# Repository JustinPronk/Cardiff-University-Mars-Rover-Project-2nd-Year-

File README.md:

# Rover Control PCB

Custom PCB for driving and monitoring a motor-based rover platform. Handles motor control, regulated power distribution, and onboard environmental sensing.

## Overview

- **Motor driver:** L298N dual H-bridge driving up to 4 outputs (OUT1–OUT4), with flyback diode protection (D1–D8) on each leg.
- **Power distribution:** 12V input regulated down to 5V (KA78M05) and 3.3V (LT1129), with status LED indicator.
- **Sensing:** HDC2080 temperature/humidity sensor (I2C) and an LM334 current-source-based temperature reference circuit.
- **I/O:** 12-pin power/control input connector (J3) and 6-pin motor output connector (J1).

## Schematic

## PCB Layout

## 3D Render

## Bill of Materials (key parts)

| Ref | Part | Function |
|-----|------|----------|
| U5 | L298N | Dual H-bridge motor driver |
| U7 | KA78M05 (TO-252) | 5V linear regulator |
| U1 | LT1129-3.3 (SO-8) | 3.3V linear regulator |
| U6 | LM334M | Current source (temperature reference) |
| U4 | HDC2080 | Temperature/humidity sensor (I2C) |
| D1–D8 | 1N4148WT | Flyback diodes for motor outputs |
| D9 | LED | Power/status indicator |

## Status

Routed on 2 layers with a solid ground pour on the back copper. DRC clean. Pending: final fab check and enclosure/mounting fit.

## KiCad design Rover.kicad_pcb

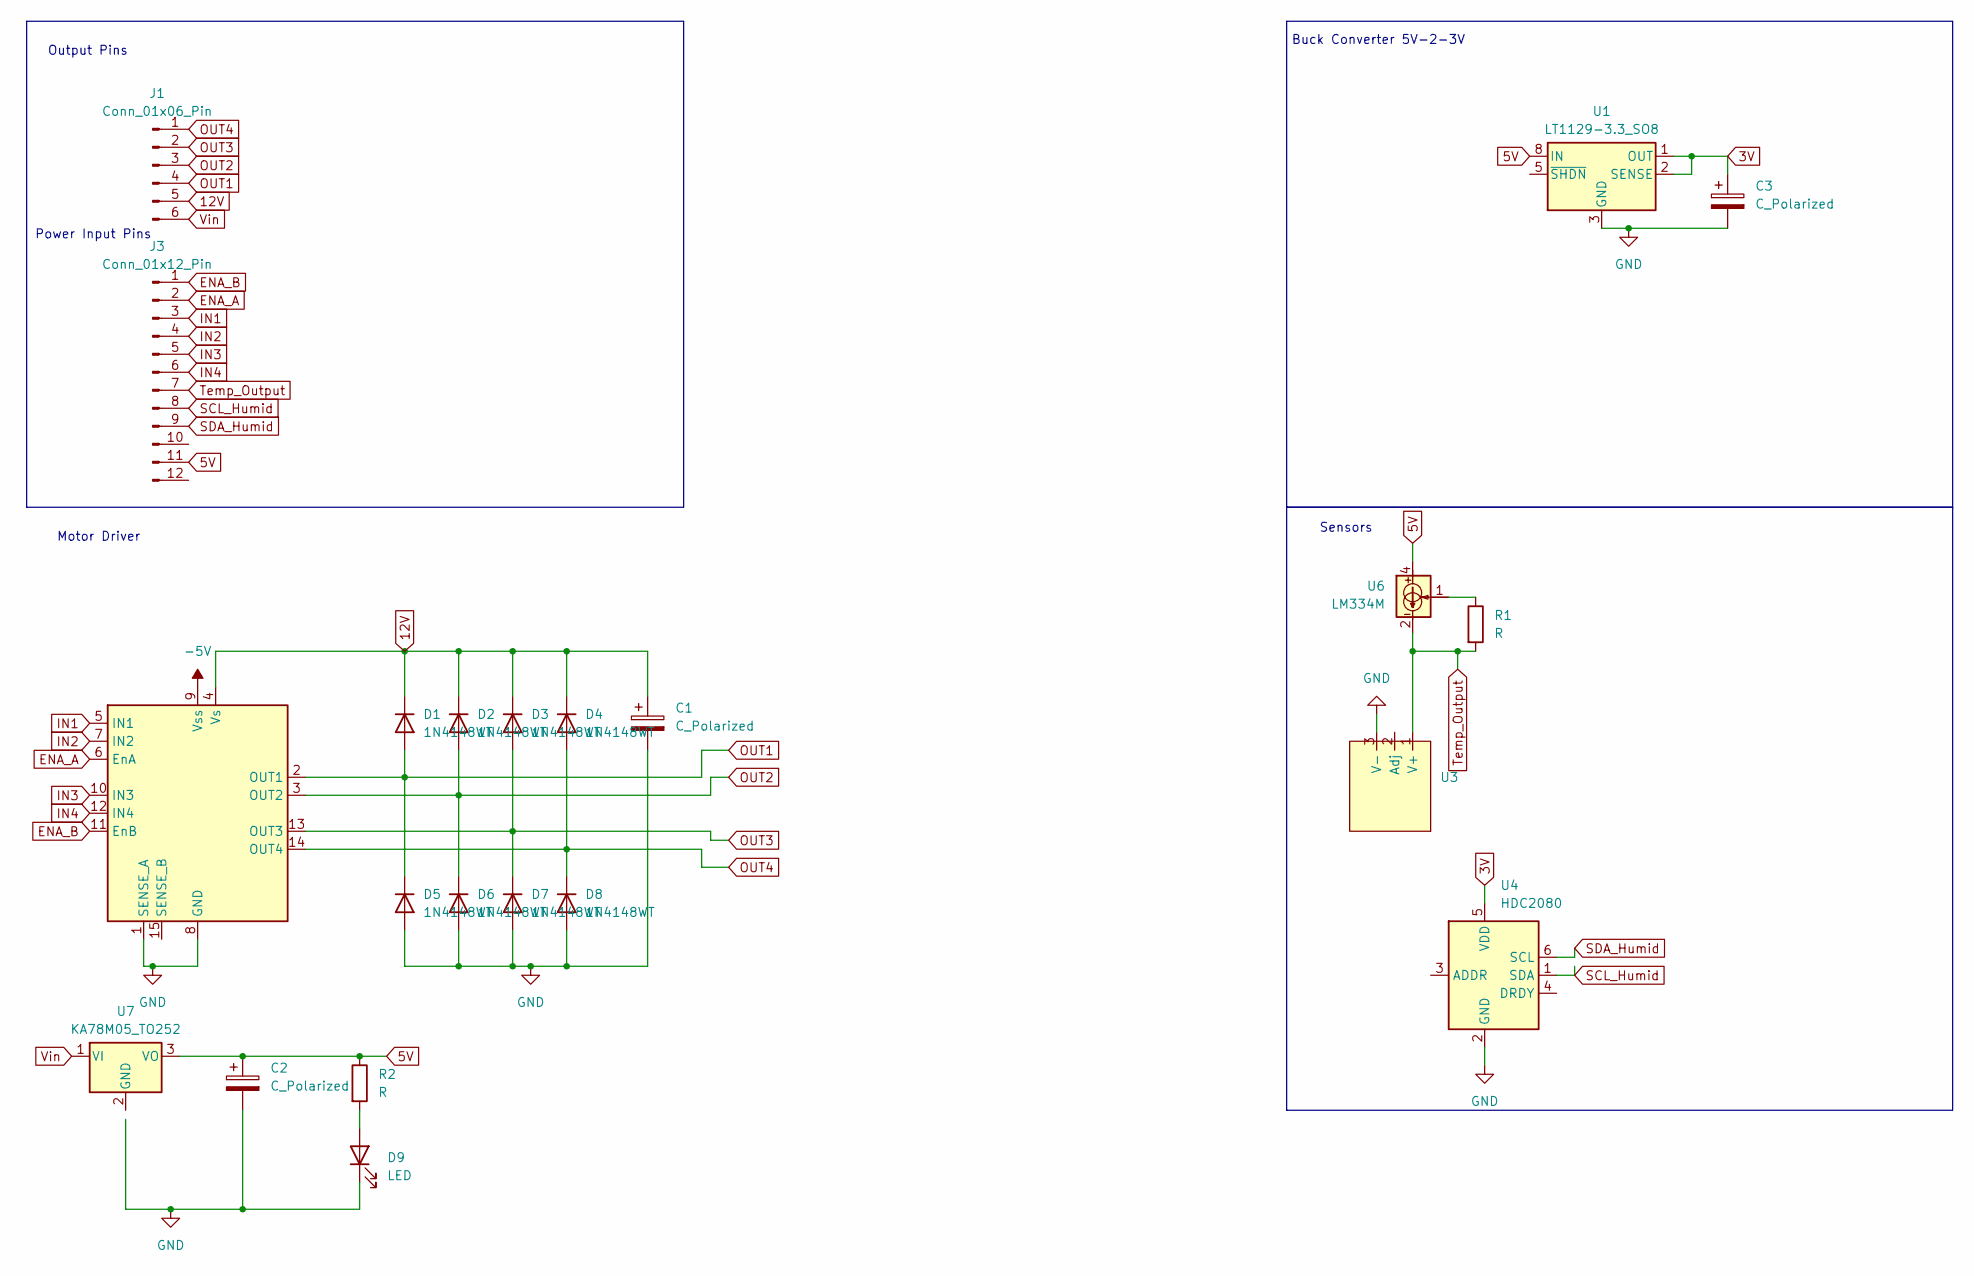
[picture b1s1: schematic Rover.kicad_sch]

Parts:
C1, C2, C3: C_Polarized; C_0201_0603Metric
D1, D2, D3, D4, D5, D6, D7, D8: 1N4148WT; D_SOD-523
D9: LED; LED_0201_0603Metric
J1: Conn_01x06_Pin; PinHeader_1x06_P2.00mm_Vertical
J3: Conn_01x12_Pin; PinHeader_1x12_P2.00mm_Vertical
R1, R2: R; R_0201_0603Metric
U1: LT1129-3.3_SO8; SOIC-8_3.9x4.9mm_P1.27mm
U3: TO92_STM
U4: HDC2080; Texas_S-PWSON-N6-HDC2080
U5: L298N; TO-220-15_P2.54x5.08mm_StaggerOdd_Lead4.58mm_Vertical
U6: LM334M; SOIC-8_3.9x4.9mm_P1.27mm
U7: KA78M05_TO252; TO-252-2

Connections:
3V: C3.1, U1.1 (OUT), U1.2 (SENSE), U4.5 (VDD)
5V: C2.1, J3.11, R2.1, U1.8 (IN), U6.4, U7.3 (VO)
12V: C1.1, D1.1 (K), D2.1 (K), D3.1 (K), D4.1 (K), J1.5, U5.4 (Vs)
-5V: U5.9 (Vss)
ENA_A: J3.2, U5.6 (EnA)
ENA_B: J3.1, U5.11 (EnB)
GND: C1.2, C2.2, C3.2, D5.2 (A), D6.2 (A), D7.2 (A), D8.2 (A), D9.1 (K), U1.3 (GND), U1.6 (GND), U1.7 (GND), U3.3 (V-), U4.2 (GND), U5.1 (SENSE_A), U5.8 (GND)
IN1: J3.3, U5.5 (IN1)
IN2: J3.4, U5.7 (IN2)
IN3: J3.5, U5.10 (IN3)
IN4: J3.6, U5.12 (IN4)
unnamed: D9.2 (A), R2.2
unnamed: R1.1, U6.1
OUT1: D1.2 (A), D5.1 (K), J1.4, U5.2 (OUT1)
OUT2: D2.2 (A), D6.1 (K), J1.3, U5.3 (OUT2)
OUT3: D3.2 (A), D7.1 (K), J1.2, U5.13 (OUT3)
OUT4: D4.2 (A), D8.1 (K), J1.1, U5.14 (OUT4)
SCL_Humid: J3.8, U4.1 (SDA)
SDA_Humid: J3.9, U4.6 (SCL)
Temp_Output: J3.7, R1.2, U3.1 (V+), U6.2, U6.3, U6.6, U6.7
Vin: J1.6, U7.1 (VI)

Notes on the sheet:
Motor Driver
Sensors
Buck Converter 5V-2-3V
Power Input Pins
Output Pins

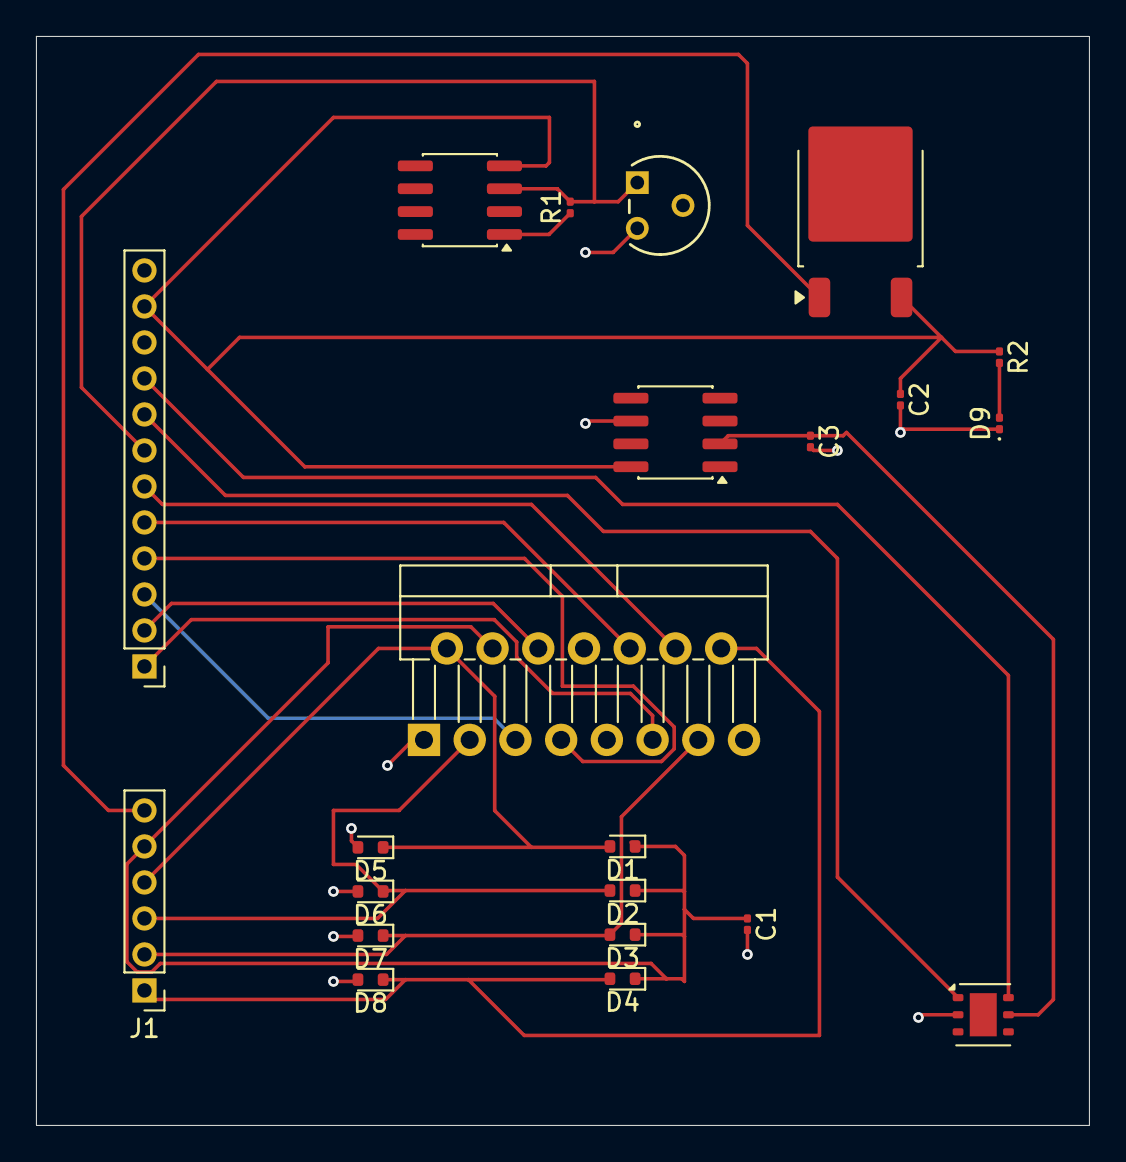
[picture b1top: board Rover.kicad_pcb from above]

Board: 2 copper layers, 58.5 x 60.5 mm, 22 parts (0 on the bottom side), 20 nets.
